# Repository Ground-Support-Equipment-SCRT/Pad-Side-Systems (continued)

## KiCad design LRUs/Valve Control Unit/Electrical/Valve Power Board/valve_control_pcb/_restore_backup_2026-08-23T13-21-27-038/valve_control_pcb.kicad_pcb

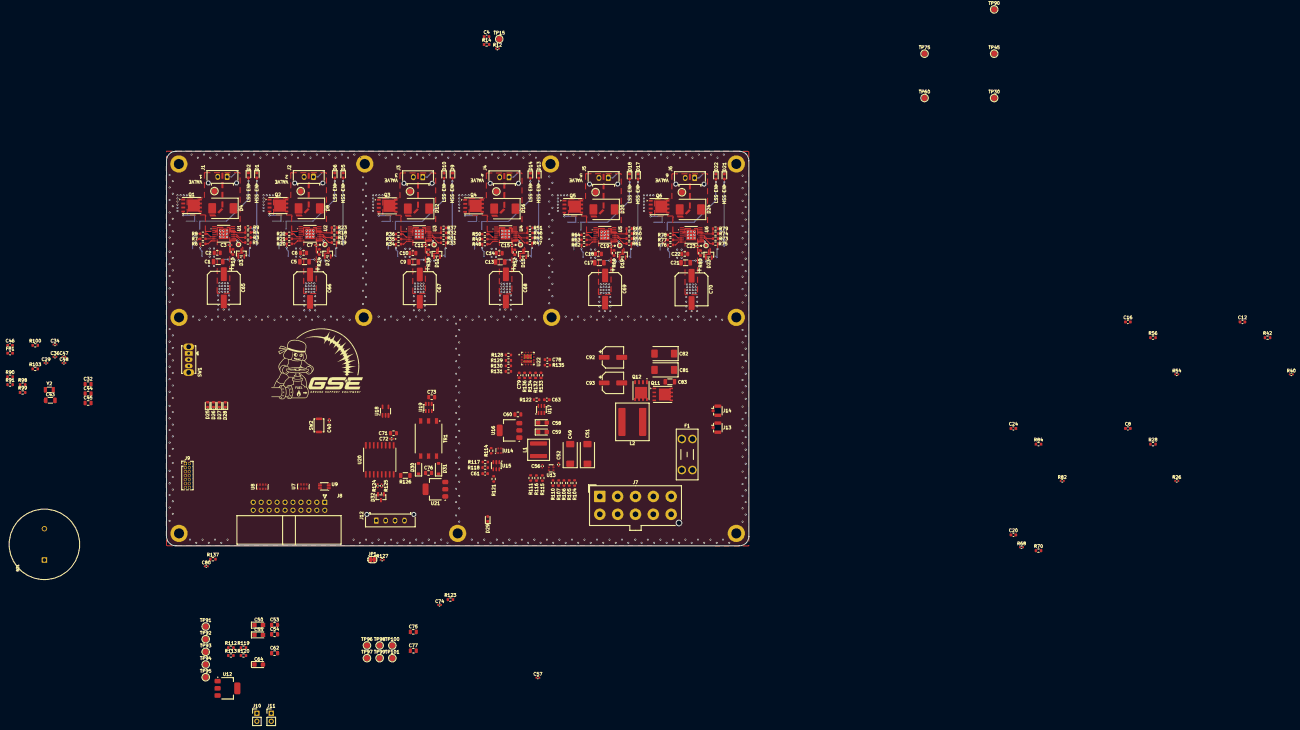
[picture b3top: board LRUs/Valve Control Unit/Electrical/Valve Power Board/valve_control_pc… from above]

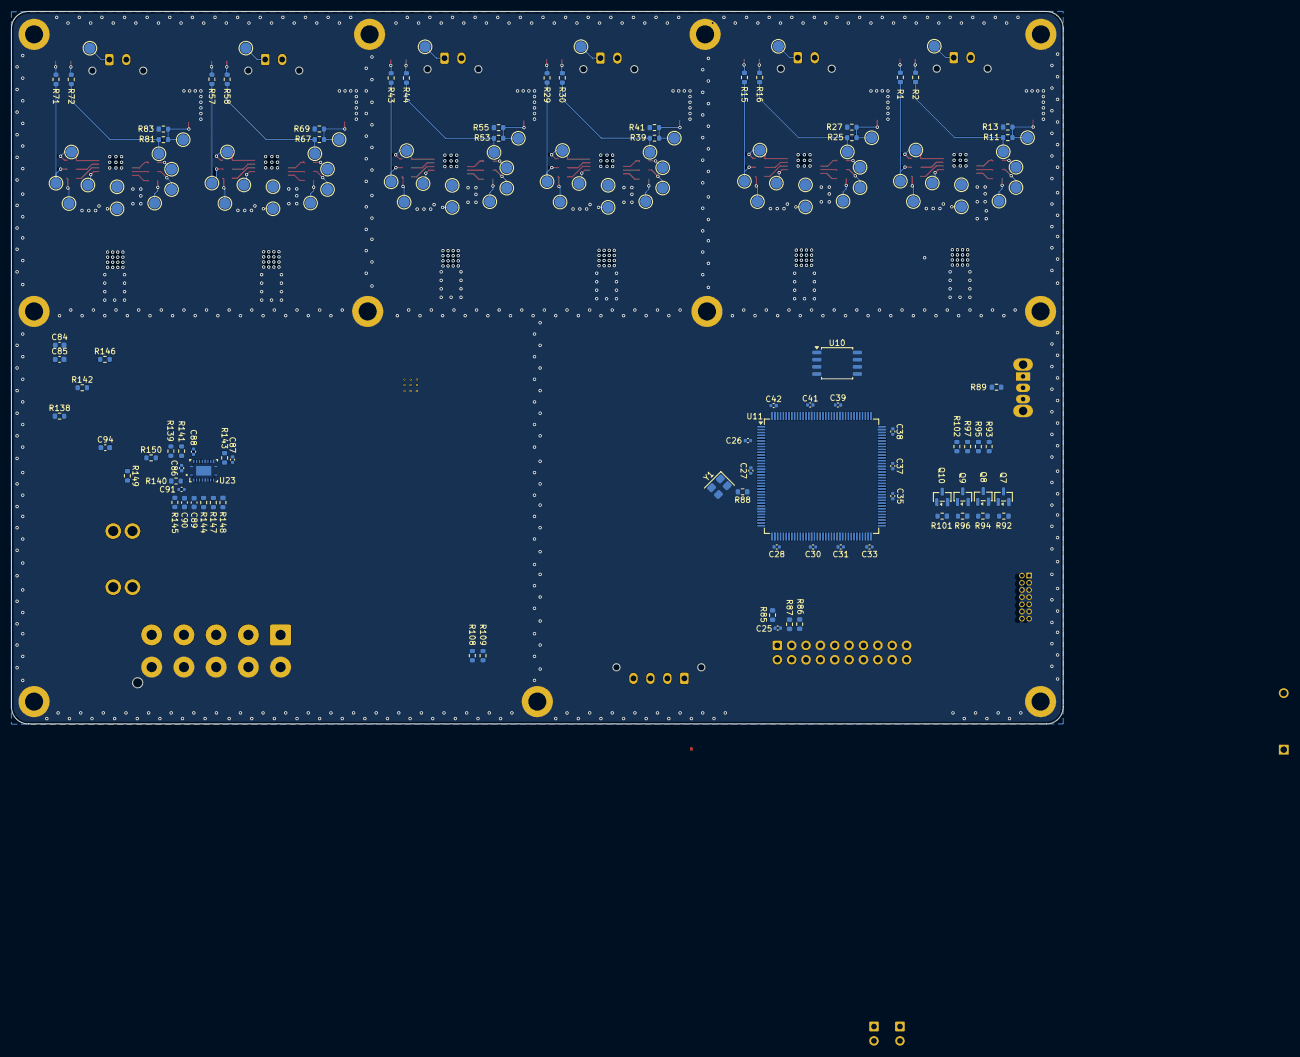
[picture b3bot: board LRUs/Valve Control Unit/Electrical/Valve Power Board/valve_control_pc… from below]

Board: 4 copper layers, 186.0 x 126.0 mm, 448 parts (154 on the bottom side), 235 nets.

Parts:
BZ1: Buzzer; MURATA_ELECTRONICS_NORTH_AMERICA_PKM22EPPH2002-B0_0
C1, C5, C9, C13, C17, C21, C43, C83: 4.7uF; C_1206_3216Metric
C2, C6, C10, C14, C18, C22: 220nF; C_0805_2012Metric
C3, C7, C11, C15, C19, C23, C26, C27, C28, C29, C30, C31, C33, C35, C37, C38, C39, C40, C41, C42, C52, C56, C57, C72, C74, C80, C86, C88: 100nF; C_0402_1005Metric
C4, C8, C12, C16, C20, C24, C46, C61, C63, C78: 10nF; C_0603_1608Metric
C25: 100pF; C_0402_1005Metric
C32, C44, C45, C53, C54, C60, C62, C71: 1uF; C_0805_2012Metric
C34, C36: 20pF; C_0402_1005Metric
C47, C48, C87, C91: 10pF; C_0402_1005Metric
C49, C51, C81, C82: 10uF; CP_EIA-7343-31_Kemet-D
C50, C55, C58, C59, C64: 10uF; CP_EIA-3216-18_Kemet-A
C65, C66, C67, C68, C69, C70: 120uF; CP_Elec_10x12.6
C73, C75, C76, C77: 10uF; C_0805_2012Metric
C79, C84: 47nF; C_0603_1608Metric
C85: 2.2uF; C_0603_1608Metric
C89, C90, C94: 330pF; C_0603_1608Metric
C92, C93: 47uF; CP_Elec_6.3x5.4
D1, D2, D5, D6, D9, D10, D13, D14, D17, D18, D21, D22, D29: RED; LED_0603_1608Metric
D3, D7, D11, D15, D19, D23: BAS21; SOT-23
D4, D8, D12, D16, D20, D24: S3M-E3/57T; D_SMC
D25, D26, D27, D28: WHITE; LED_0603_1608Metric
D30, D31: MBR0520LT; D_SOD-123
D32: SM712_SOT23; SOT-23
F1: 0297020; Fuseholder_Blade_Mini_Keystone_3568
FB1: 120R; L_0603_1608Metric
H1, H2, H3, H4, H5, H6, H7, H8, H9, H10, H11: MountingHole_Pad; MountingHole_3.2mm_M3_ISO14580_Pad
J1, J2, J3, J4, J5, J6: 0436500215; Molex_Micro-Fit_3.0_43650-0215_1x02_P3.00mm_Vertical
J7: 0768290110; Molex_Mega-Fit_76829-0110_2x05_P5.70mm_Vertical
J8: Conn_02x10_Odd_Even; IDC-Header_2x10_P2.54mm_Horizontal
J9: Conn_ST_STDC14; PinHeader_2x07_P1.27mm_Vertical
J10: Conn_01x02_Pin; PinHeader_1x02_P2.54mm_Vertical
J11: 01x02_PinHeader; PinHeader_1x02_P2.54mm_Vertical
J12: Conn_01x04; Molex_Micro-Fit_3.0_43650-0415_1x04_P3.00mm_Vertical
J13, J14: Conn_Coaxial; U.FL_Hirose_U.FL-R-SMT-1_Vertical
JP1: SolderJumper_2_Bridged; SolderJumper-2_P1.3mm_Bridged_RoundedPad1.0x1.5mm
L1: 15uH; L_Coilcraft_XAL6060-XXX
L2: 4.7uH; L_Coilcraft_XAL1010-XXX
Q1, Q2, Q3, Q4, Q5, Q6, Q11, Q12: SiR882ADP; PowerPAK_SO-8_Single
Q7, Q8, Q9, Q10: AO3400A; SOT-23
R1, R2, R10, R15, R16, R24, R29, R30, R38, R43, R44, R52, R57, R58, R66, R71, R72, R80, R86, R87, R93, R95, R97, R102: 4.7k; R_0603_1608Metric
R3, R4, R5, R6, R7, R8, R14, R17, R18, R19, R20, R21, R22, R28, R31, R32, R33, R34, R35, R36, R42, R45, R46, R47, R48, R49, R50, R56, R59, R60, R61, R62, R63, R64, R70, R73, R74, R75, R76, R77, R78, R84: 15k; R_0603_1608Metric
R9, R23, R37, R51, R65, R79, R89, R113, R121, R122, R123, R131, R135: 10k; R_0603_1608Metric
R11, R25, R39, R53, R67, R81, R90, R136, R144: 100; R_0603_1608Metric
R12, R26, R40, R54, R68, R82: 680; R_0402_1005Metric
R13, R27, R41, R55, R69, R83, R92, R94, R96, R101, R111, R114: 47k; R_0603_1608Metric
R85: 200k; R_0603_1608Metric
R88: 390; R_0603_1608Metric
R91: 1M; R_0603_1608Metric
R98, R99, R100, R103, R110, R132, R133: 0; R_0603_1608Metric
R104: 220k; R_0603_1608Metric
R105, R112, R138, R142: 20k; R_0603_1608Metric
R106, R134: 9.1k; R_0603_1608Metric
R107, R120: 51k; R_0603_1608Metric
R108, R109: 2.2k; R_0603_1608Metric
R115, R139: 68k; R_0603_1608Metric
R116: 13k; R_0603_1608Metric
R117, R119, R128: 150k; R_0603_1608Metric
R118: 100k; R_0603_1608Metric
R124, R125: 10; R_0402_1005Metric
R126: 0; R_1206_3216Metric
R127: 120; R_0402_1005Metric
R129, R146: 18k; R_0603_1608Metric
R130: 27k; R_0603_1608Metric
R137: 1k; R_0603_1608Metric
R140: 8.2k; R_0603_1608Metric
R141: 2; R_0603_1608Metric
R143: 680; R_0603_1608Metric
R145: 1.8k; R_0603_1608Metric
R147: 1.2k; R_0603_1608Metric
R148, R150: 75; R_0603_1608Metric
R149: 10; R_0603_1608Metric
SW1: SW_SPDT; SW_Slide_SPDT_Straight_CK_OS102011MS2Q
SW2: SW_Push; SW_Push_SPST_NO_Alps_SKRK
TP1, TP2, TP3, TP4, TP5, TP6, TP7, TP8, TP10, TP11, TP12, TP13, TP14, TP15, TP16, TP17, TP18, TP19, TP20, TP21, TP22, TP23, TP25, TP26, TP27, TP28, TP29, TP30, TP31, TP32, TP33, TP34, TP35, TP36, TP37, TP38, TP40, TP41, TP42, TP43, TP44, TP45, TP46, TP47, TP48, TP49, TP50, TP51, TP52, TP53, TP55, TP56, TP57, TP58, TP59, TP60, TP61, TP62, TP63, TP64, TP65, TP66, TP67, TP68, TP70, TP71, TP72, TP73, TP74, TP75, TP76, TP77, TP78, TP79, TP80, TP81, TP82, TP83, TP85, TP86, TP87, TP88, TP89, TP90, TP91, TP92, TP93, TP94, TP95, TP96, TP97, TP98, TP99, TP100, TP101: TestPoint; TestPoint_Pad_D2.0mm
TP9, TP24, TP39, TP54, TP69, TP84: TestPoint; TestPoint_Pad_D1.0mm
TR1: 750315371; Transformer_Wuerth_750315371
U1, U2, U3, U4, U5, U6: TPS27SA08CPWPR; TSSOP_CPWPR_TEX
U7, U8: TPD6E05U06RVZ; Texas_R-PUSON-N14
U9: PCA9306DC; VSSOP-8_2.3x2mm_P0.5mm
U10: W25Q128JVS; SOIC-8_5.3x5.3mm_P1.27mm
U11: STM32L496ZGTx; LQFP-144_20x20mm_P0.5mm
U12, U16: AMS1117-3.3; SOT-223-3_TabPin2
U13: TPS62933P; SOT-583-8
U14: TPS2116DRL; SOT-583-8
U15, U17: TPS22810DBV; SOT-23-6
U18: 74LVC1G17; SOT-23-5_HandSoldering
U19: SN6505BDBV; SOT-23-6
U20: ISO1450BDWR; SOIC127P1030X265-16N
U21: AMS1117-5.0; SOT-223-3_TabPin2
U22: IC_TPS259830ONRGER
U23: LM5145RGYR
Y1: 8MHz; Crystal_SMD_3225-4Pin_3.2x2.5mm
Y2: 32KHz; Crystal_SMD_3215-2Pin_3.2x1.5mm

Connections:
3V3_EXT: J8.2, U9.2 (VREF1)
+3V3: C25.1, C26.1, C27.1, C28.1, C30.1, C31.1, C33.1, C35.1, C37.1, C38.1, C39.1, C41.1, C42.1, C43.1, C44.1, FB1.1, J9.3 (VCC), R9.1, R23.1, R37.1, R51.1, R65.1, R79.1, R85.2, R86.2, R87.2, R111.1, R121.2, R135.1, SW1.3 (C), U9.7 (VREF2), U11.6 (VBAT), U11.17 (VDD), U11.39 (VDD), U11.52 (VDD), U11.62 (VDD), U11.72 (VDD), U11.84 (VDD), U11.95 (VDDIO2), U11.106 (VDDUSB), U11.108 (VDD), U11.121 (VDD), U11.131 (VDDIO2), U11.144 (VDD), U15.6 (VOUT), U18.5 (VCC)
+5V: C71.1, C72.1, C73.1, R93.2, R95.2, R97.2, R102.2, R122.2, R123.1, TR1.2, U17.6 (VOUT), U19.2 (VCC), U19.5 (EN), U20.1 (VCC1)
/Connectors/I2C_MASTER_SCL: J8.1, U7.14 (D1+), U9.3 (SCL1)
/Connectors/I2C_MASTER_SDA: J8.4, U7.13 (D1-), U9.4 (SDA1)
/Connectors/I2C_SCL: R86.1, U9.6 (SCL2)
/Connectors/I2C_SDA: R87.1, U9.5 (SDA2)
/Connectors/PIN5: J8.5, U7.12 (D2+)
/Connectors/PIN8: J8.8, U7.11 (D2-)
/Connectors/PIN9: J8.9, U7.9 (D3+)
/Connectors/PIN12: J8.12, U7.8 (D3-)
/Connectors/PIN13: J8.13, U8.14 (D1+)
/Connectors/PIN16: J8.16, U8.13 (D1-)
/Connectors/PIN17: J8.17, U8.12 (D2+)
/Connectors/PIN20: J8.20, U8.11 (D2-)
/Root/RS_485/A_RX_MAIN_N: R125.2, U20.13 (B)
/Root/RS_485/A_RX_MAIN_P: R124.2, U20.12 (A)
/Root/RS_485/RX_MAIN_N: D32.1 (A1), J12.2, JP1.1 (A), R125.1
/Root/RS_485/RX_MAIN_P: D32.2 (A2), J12.1, R124.1, R127.2
/Root/stm32_microcontroller/BOOT: R89.1, U11.138 (PH3)
/Root/stm32_microcontroller/D1: Q7.1 (G), R92.1, U11.82 (PD13)
/Root/stm32_microcontroller/D2: Q8.1 (G), R94.1, U11.81 (PD12)
/Root/stm32_microcontroller/D3: Q9.1 (G), R96.1, U11.80 (PD11)
/Root/stm32_microcontroller/D4: Q10.1 (G), R101.1, U11.79 (PD10)
/Root/stm32_microcontroller/JTDI: J9.10 (JTDI/NC), R103.1
/Root/stm32_microcontroller/JTDO: J9.8 (JTDO/SWO), R98.1
/Root/stm32_microcontroller/NRST: C40.2, J9.12 (~RST), SW2.2, U11.25 (NRST)
/Root/stm32_microcontroller/VDDA: C45.1, C46.1, FB1.2, U11.33 (VDDA)
/System Power/3V3_STATUS: R114.2, U14.8 (ST)
/System Power/5V_MAIN_PG: R111.2, TP95.1 (1_1), U13.7 (PG)
/System Power/V-3P3_LDO: C62.1, C64.1, R112.2, U14.3 (VIN1), U14.5 (MODE), U16.2 (VO)
/System Power/V-5P0_BUCK: C57.1, C58.1, C59.1, C60.1, L1.2, R108.1, R115.1, R119.2, U16.3 (VI), U17.1 (VIN)
/System Power/VEN: R106.1, R107.1, TP92.1 (1_1), U13.2 (EN)
/System Power/VFB: R115.2, R116.1, TP93.1 (1_1), U13.8 (FB)
/Valves/12V_main/SENSE_OUT: J14.1 (In), R146.2, R149.1, R150.2
/Valves/12V_main/VOUT_MAIN: C92.1, C93.1, J13.1 (In), L2.2, R128.2, R149.2, U22.1 (IN), U22.2 (IN), U22.3 (IN), U22.16 (IN), U22.25 (IN), U22.27 (EPAD), U22.28 (EPAD), U22.29 (EPAD), U22.30 (EPAD), U22.31 (EPAD), U22.32 (EPAD)
/Valves/Valve 1/12V_OUT+: D4.1 (K), J1.1, TP13.1 (1_1), U1.6 (VOUT), U1.7 (VOUT), U1.8 (VOUT), U1.9 (VOUT), U1.10 (VOUT), U1.11 (VOUT)
/Valves/Valve 1/12V_OUT-: D4.2 (A), J1.2, Q1.5 (D), TP14.1 (1_1)
/Valves/Valve 1/LFET_GATE: Q1.4 (G), R11.1, R13.1, TP11.1 (1_1)
/Valves/Valve 1/LSW_DIA_EN_PROT: R6.1, U1.16 (DIA_EN)
/Valves/Valve 1/LSW_LATCH_PROT: R5.1, U1.3 (LATCH)
/Valves/Valve 1/LSW_SEL1_PROT: R8.1, U1.14 (SEL1)
/Valves/Valve 1/LSW_SEL2_PROT: R7.1, U1.15 (SEL2)
/Valves/Valve 1/LSW_SNS_PROT: R12.2, R14.2, TP12.1 (1_1), U1.2 (SNS)
/Valves/Valve 1/VIN: C1.1, C2.1, C3.1, C5.1, C6.1, C7.1, C9.1, C10.1, C11.1, C13.1, C14.1, C15.1, C17.1, C18.1, C19.1, C21.1, C22.1, C23.1, C65.1, C66.1, C67.1, C68.1, C69.1, C70.1, TP3.1 (1_1), TP18.1 (1_1), TP33.1 (1_1), TP48.1 (1_1), TP63.1 (1_1), TP78.1 (1_1), U1.EPAD (VBB), U2.EPAD (VBB), U3.EPAD (VBB), U4.EPAD (VBB), U5.EPAD (VBB), U6.EPAD (VBB), U22.17 (OUT), U22.18 (OUT), U22.19 (OUT), U22.20 (OUT), U22.21 (OUT), U22.22 (OUT), U22.23 (OUT), U22.24 (OUT)
/Valves/Valve 1/~LSW_ST_PROT: R4.1, R9.2, U1.5 (~ST)
/Valves/Valve 2/12V_OUT+: D8.1 (K), J2.1, TP28.1 (1_1), U2.6 (VOUT), U2.7 (VOUT), U2.8 (VOUT), U2.9 (VOUT), U2.10 (VOUT), U2.11 (VOUT)
/Valves/Valve 2/12V_OUT-: D8.2 (A), J2.2, Q2.5 (D), TP29.1 (1_1)
/Valves/Valve 2/LFET_GATE: Q2.4 (G), R25.1, R27.1, TP26.1 (1_1)
/Valves/Valve 2/LSW_DIA_EN_PROT: R20.1, U2.16 (DIA_EN)
/Valves/Valve 2/LSW_LATCH_PROT: R19.1, U2.3 (LATCH)
/Valves/Valve 2/LSW_SEL1_PROT: R22.1, U2.14 (SEL1)
/Valves/Valve 2/LSW_SEL2_PROT: R21.1, U2.15 (SEL2)
/Valves/Valve 2/LSW_SNS_PROT: R26.2, R28.2, TP27.1 (1_1), U2.2 (SNS)
/Valves/Valve 2/~LSW_ST_PROT: R18.1, R23.2, U2.5 (~ST)
/Valves/Valve 3/12V_OUT+: D12.1 (K), J3.1, TP43.1 (1_1), U3.6 (VOUT), U3.7 (VOUT), U3.8 (VOUT), U3.9 (VOUT), U3.10 (VOUT), U3.11 (VOUT)
/Valves/Valve 3/12V_OUT-: D12.2 (A), J3.2, Q3.5 (D), TP44.1 (1_1)
/Valves/Valve 3/LFET_GATE: Q3.4 (G), R39.1, R41.1, TP41.1 (1_1)
/Valves/Valve 3/LSW_DIA_EN_PROT: R34.1, U3.16 (DIA_EN)
/Valves/Valve 3/LSW_LATCH_PROT: R33.1, U3.3 (LATCH)
/Valves/Valve 3/LSW_SEL1_PROT: R36.1, U3.14 (SEL1)
/Valves/Valve 3/LSW_SEL2_PROT: R35.1, U3.15 (SEL2)
/Valves/Valve 3/LSW_SNS_PROT: R40.2, R42.2, TP42.1 (1_1), U3.2 (SNS)
/Valves/Valve 3/~LSW_ST_PROT: R32.1, R37.2, U3.5 (~ST)
/Valves/Valve 4/12V_OUT+: D16.1 (K), J4.1, TP58.1 (1_1), U4.6 (VOUT), U4.7 (VOUT), U4.8 (VOUT), U4.9 (VOUT), U4.10 (VOUT), U4.11 (VOUT)
/Valves/Valve 4/12V_OUT-: D16.2 (A), J4.2, Q4.5 (D), TP59.1 (1_1)
/Valves/Valve 4/LFET_GATE: Q4.4 (G), R53.1, R55.1, TP56.1 (1_1)
/Valves/Valve 4/LSW_DIA_EN_PROT: R48.1, U4.16 (DIA_EN)
/Valves/Valve 4/LSW_LATCH_PROT: R47.1, U4.3 (LATCH)
/Valves/Valve 4/LSW_SEL1_PROT: R50.1, U4.14 (SEL1)
/Valves/Valve 4/LSW_SEL2_PROT: R49.1, U4.15 (SEL2)
/Valves/Valve 4/LSW_SNS_PROT: R54.2, R56.2, TP57.1 (1_1), U4.2 (SNS)
/Valves/Valve 4/~LSW_ST_PROT: R46.1, R51.2, U4.5 (~ST)
/Valves/Valve 5/12V_OUT+: D20.1 (K), J5.1, TP73.1 (1_1), U5.6 (VOUT), U5.7 (VOUT), U5.8 (VOUT), U5.9 (VOUT), U5.10 (VOUT), U5.11 (VOUT)
/Valves/Valve 5/12V_OUT-: D20.2 (A), J5.2, Q5.5 (D), TP74.1 (1_1)
/Valves/Valve 5/LFET_GATE: Q5.4 (G), R67.1, R69.1, TP71.1 (1_1)
/Valves/Valve 5/LSW_DIA_EN_PROT: R62.1, U5.16 (DIA_EN)
/Valves/Valve 5/LSW_LATCH_PROT: R61.1, U5.3 (LATCH)
/Valves/Valve 5/LSW_SEL1_PROT: R64.1, U5.14 (SEL1)
/Valves/Valve 5/LSW_SEL2_PROT: R63.1, U5.15 (SEL2)
/Valves/Valve 5/LSW_SNS_PROT: R68.2, R70.2, TP72.1 (1_1), U5.2 (SNS)
/Valves/Valve 5/~LSW_ST_PROT: R60.1, R65.2, U5.5 (~ST)
/Valves/Valve 6/12V_OUT+: D24.1 (K), J6.1, TP88.1 (1_1), U6.6 (VOUT), U6.7 (VOUT), U6.8 (VOUT), U6.9 (VOUT), U6.10 (VOUT), U6.11 (VOUT)
/Valves/Valve 6/12V_OUT-: D24.2 (A), J6.2, Q6.5 (D), TP89.1 (1_1)
/Valves/Valve 6/LFET_GATE: Q6.4 (G), R81.1, R83.1, TP86.1 (1_1)
/Valves/Valve 6/LSW_DIA_EN_PROT: R76.1, U6.16 (DIA_EN)
/Valves/Valve 6/LSW_LATCH_PROT: R75.1, U6.3 (LATCH)
/Valves/Valve 6/LSW_SEL1_PROT: R78.1, U6.14 (SEL1)
/Valves/Valve 6/LSW_SEL2_PROT: R77.1, U6.15 (SEL2)
/Valves/Valve 6/LSW_SNS_PROT: R82.2, R84.2, TP87.1 (1_1), U6.2 (SNS)
/Valves/Valve 6/~LSW_ST_PROT: R74.1, R79.2, U6.5 (~ST)
/Valves/master_efuse/DVDT: C78.1, U22.15 (DVDT/BGATE)
/Valves/master_efuse/ILIM: R136.2, U22.8 (ILIM)
/Valves/master_efuse/IMON_IC: R134.2, R137.2, U22.9 (IMON)
/Valves/master_efuse/ITIM: C79.1, U22.7 (ITIMER)
EFUSE_IMON: C80.1, R137.1
EFUSE_PG: R135.2, U22.13 (PG)
GND: BZ1.2 (-), C1.2, C2.2, C4.2, C5.2, C6.2, C8.2, C9.2, C10.2, C12.2, C13.2, C14.2, C16.2, C17.2, C18.2, C20.2, C21.2, C22.2, C24.2, C25.2, C26.2, C27.2, C28.2, C29.2, C30.2, C31.2, C32.2, C33.2, C34.2, C35.2, C36.2, C37.2, C38.2, C39.2, C40.1, C41.2, C42.2, C43.2, C44.2, C45.2, C46.2, C47.2, C48.2, C49.2, C50.2, C51.2, C52.2, C53.2, C54.2, C55.2, C57.2, C58.2, C59.2, C60.2, C61.2, C62.2, C63.2, C64.2, C65.2, C66.2, C67.2, C68.2, C69.2, C70.2, C71.2, C72.2, C73.2, C78.2, C79.2, C80.2, C81.2, C82.2, C83.2, C84.2, C85.2, C86.2, C87.2, C92.2, C93.2, D1.1 (K), D2.1 (K), D3.1 (A), D5.1 (K), D6.1 (K), D7.1 (A), D9.1 (K), D10.1 (K), D11.1 (A), D13.1 (K), D14.1 (K), D15.1 (A), D17.1 (K), D18.1 (K), D19.1 (A), D21.1 (K), D22.1 (K), D23.1 (A), D29.1 (K), H1.1 (1_1), H2.1 (1_1), H3.1 (1_1), H4.1 (1_1), H5.1 (1_1), H6.1 (1_1), H7.1 (1_1), H8.1 (1_1), H9.1 (1_1), H10.1 (1_1), H11.1 (1_1), J7.6, J7.7, J7.8, J7.9, J7.10, J8.3, J8.6, J8.7, J8.10, J8.11, J8.14, J8.15, J8.18, J8.19, J9.5 (GND), J9.7 (GND), J9.11 (GNDDetect), J10.2, J11.2, J13.2 (Ext), J14.2 (Ext), Q1.1 (S), Q1.2 (S), Q1.3 (S), Q2.1 (S), Q2.2 (S), Q2.3 (S), Q3.1 (S), Q3.2 (S), Q3.3 (S), Q4.1 (S), Q4.2 (S), Q4.3 (S), Q5.1 (S), Q5.2 (S), Q5.3 (S), Q6.1 (S), Q6.2 (S), Q6.3 (S), Q7.2 (S), Q8.2 (S), Q9.2 (S), Q10.2 (S), Q12.1 (S), Q12.2 (S), Q12.3 (S), R10.1, R12.1, R13.2, R24.1, R26.1, R27.2, R38.1, R40.1, R41.2, R52.1, R54.1, R55.2, R66.1, R68.1, R69.2, R80.1, R82.1, R83.2, R91.1, R92.2, R94.2, R96.2, R101.2, R107.2, R110.1, R113.2, R116.2, R118.1, R120.2, R131.1, R132.1, R133.1, R134.1, R136.1, R138.1, R140.1, R148.1, SW1.1 (A), SW2.1, TP10.1 (1_1), TP25.1 (1_1), TP40.1 (1_1), TP55.1 (1_1), TP70.1 (1_1), TP85.1 (1_1), U7.5 (GND), U7.10 (GND), U8.5 (GND), U8.10 (GND), U9.1 (GND), U11.16 (VSS), U11.30 (VSSA), U11.31 (VREF-), U11.38 (VSS), U11.51 (VSS), U11.61 (VSS), U11.71 (VSS), U11.83 (VSS), U11.94 (VSS), U11.107 (VSS), U11.120 (VSS), U11.130 (VSS), U11.143 (VSS), U12.1 (GND), U13.4 (GND), U14.1 (GND), U15.2 (GND), U16.1 (GND), U17.2 (GND), U18.3 (GND), U19.4 (GND), U19.6 (CLK), U20.2 (GND1), U20.8 (GND1__1), U22.4 (GND), U22.5 (GND), U22.14 (GND), U22.26 (GND), U22.33 (EPAD), U22.34 (EPAD), U22.35 (EPAD), U23.6 (AGND), U23.12 (PGND), U23.15 (EP), U23.21 (EP), Y1.2, Y1.4
ISOGND: C74.2, C75.2, C76.2, C77.2, D32.3 (common), J12.3, TR1.5, U20.9 (GND2), U20.15 (GND2__1), U21.1 (GND)
MODGND: C3.2, C7.2, C11.2, C15.2, C19.2, C23.2, D3.3 (K), D7.3 (K), D11.3 (K), D15.3 (K), D19.3 (K), D23.3 (K), R10.2, R24.2, R38.2, R52.2, R66.2, R80.2, TP9.1 (1_1), TP24.1 (1_1), TP39.1 (1_1), TP54.1 (1_1), TP69.1 (1_1), TP84.1 (1_1), U1.1 (GND), U2.1 (GND), U3.1 (GND), U4.1 (GND), U5.1 (GND), U6.1 (GND)
unnamed: BZ1.1 (+), R90.2
unnamed: C36.1, R88.2, Y1.3
unnamed: C89.2, C90.1
unnamed: C91.2, R145.2
unnamed: C94.1, R150.1
unnamed: D1.2 (A), R1.1
unnamed: D2.2 (A), R2.1
unnamed: D5.2 (A), R15.1
unnamed: D6.2 (A), R16.1
unnamed: D9.2 (A), R29.1
unnamed: D10.2 (A), R30.1
unnamed: D13.2 (A), R43.1
unnamed: D14.2 (A), R44.1
unnamed: D17.2 (A), R57.1
unnamed: D18.2 (A), R58.1
unnamed: D21.2 (A), R71.1
unnamed: D22.2 (A), R72.1
unnamed: D25.2 (A), R93.1
unnamed: D25.1 (K), Q7.3 (D)
unnamed: D26.2 (A), R95.1
unnamed: D26.1 (K), Q8.3 (D)
unnamed: D27.2 (A), R97.1
unnamed: D27.1 (K), Q9.3 (D)
unnamed: D28.2 (A), R102.1
unnamed: D28.1 (K), Q10.3 (D)
unnamed: D29.2 (A), R109.2
unnamed: D30.2 (A), TP98.1 (1_1), TR1.4
unnamed: C76.1, D30.1 (K), D31.1 (K), R126.2, TP100.1 (1_1), U21.3 (VI)
unnamed: D31.2 (A), TP99.1 (1_1), TR1.6
unnamed: F1.1, J7.1, J7.2, J7.3, J7.4, J7.5
unnamed: J9.13 (VCP_RX), R99.2
unnamed: J9.14 (VCP_TX), R100.2
unnamed: J10.1, R117.1, R118.2, U15.3 (EN/UVLO)
unnamed: J11.1, R119.1, R120.1, U17.3 (EN/UVLO)
unnamed: JP1.2 (B), R127.1
unnamed: Q11.4 (G), U23.18 (HO)
unnamed: C88.2, L2.1, Q11.1 (S), Q11.2 (S), Q11.3 (S), Q12.5 (D), R143.1, U23.19 (SW)
unnamed: Q12.4 (G), U23.13 (LO)
unnamed: R104.1, R105.2
unnamed: R105.1, R106.2
unnamed: R108.2, R109.1
unnamed: R128.1, R129.2
unnamed: R144.2, R145.1
unnamed: R147.1, R148.2
unnamed: R89.2, SW1.2 (B)
unnamed: R3.1, U1.4 (EN)
unnamed: R17.1, U2.4 (EN)
unnamed: R31.1, U3.4 (EN)
unnamed: R45.1, U4.4 (EN)
unnamed: R59.1, U5.4 (EN)
unnamed: R73.1, U6.4 (EN)
unnamed: R85.1, U9.8 (EN)
unnamed: C48.1, U11.8 (RCC_OSC32_IN), Y2.1
unnamed: C47.1, U11.9 (RCC_OSC32_OUT), Y2.2
unnamed: R90.1, R91.2, U11.68 (PE15)
unnamed: C34.1, U11.23 (RCC_OSC_IN), Y1.1
unnamed: R88.1, U11.24 (RCC_OSC_OUT)
unnamed: C29.1, C32.1, U11.32 (VREF+)
unnamed: C54.1, C55.1, U12.2 (VO), U14.6 (VIN2)
unnamed: C56.1, U13.6 (BST)
unnamed: R110.2, U13.1 (RT)
unnamed: C56.2, L1.1, U13.5 (SW)
unnamed: R112.1, R113.1, U14.4 (PR1)
unnamed: C61.1, U15.4 (CT)
unnamed: R121.1, U15.5 (QOD)
unnamed: R114.1, R117.2, U14.2 (VOUT), U14.7 (VOUT), U15.1 (VIN)
unnamed: C63.1, U17.4 (CT)
unnamed: R122.1, U17.5 (QOD)
unnamed: TP96.1 (1_1), TR1.3, U19.1 (D1)
unnamed: TP97.1 (1_1), TR1.1, U19.3 (D2)
unnamed: R123.2, U18.2, U20.3 (R)
unnamed: C74.1, C75.1, C77.1, R126.1, TP101.1 (1_1), U20.16 (VCC2), U21.2 (VO)
unnamed: R129.1, R130.2, U22.6 (EN/UVLO)
unnamed: R133.2, U22.11 (NRETRY)
unnamed: R130.1, R131.2, U22.12 (OVLO)
unnamed: R132.2, U22.10 (RETRY_DLY)
unnamed: C88.1, U23.17 (BST)
unnamed: C90.2, C91.1, U23.4 (COMP)
unnamed: R139.1, R140.2, U23.1 (EN_UVLO)
unnamed: C89.1, C94.2, R144.1, R146.1, R147.2, U23.5 (FB)
unnamed: C87.1, R143.2, U23.11 (ILIM)
unnamed: R138.2, U23.2 (RT)
unnamed: C84.1, U23.3 (SS_TRK)
unnamed: R142.2, U23.8 (SYNCIN)
unnamed: C85.1, R142.1, U23.14 (VCC)
unnamed: C86.1, R141.1, U23.20 (VIN)
VALVE1.LSW_DIA_EN: R6.2, TP6.1 (1_1)
VALVE1.LSW_LATCH: R5.2, TP5.1 (1_1)
VALVE1.LSW_SEL1: R8.2, TP8.1 (1_1)
VALVE1.LSW_SEL2: R7.2, TP7.1 (1_1)
VALVE1.~LSW_ST: R4.2, TP4.1 (1_1)
VALVE1_HSS_EN: R1.2, R3.2, TP1.1 (1_1)
VALVE1_LSS_EN: R2.2, R11.2, TP2.1 (1_1)
VALVE1_LSW_SNS: C4.1, R14.1, TP15.1 (1_1)
VALVE2.LSW_DIA_EN: R20.2, TP21.1 (1_1)
VALVE2.LSW_LATCH: R19.2, TP20.1 (1_1)
VALVE2.LSW_SEL1: R22.2, TP23.1 (1_1)
VALVE2.LSW_SEL2: R21.2, TP22.1 (1_1)
VALVE2.~LSW_ST: R18.2, TP19.1 (1_1)
VALVE2_HSS_EN: R15.2, R17.2, TP16.1 (1_1)
VALVE2_LSS_EN: R16.2, R25.2, TP17.1 (1_1)
VALVE2_LSW_SNS: C8.1, R28.1, TP30.1 (1_1)
VALVE3.LSW_DIA_EN: R34.2, TP36.1 (1_1)
VALVE3.LSW_LATCH: R33.2, TP35.1 (1_1)
VALVE3.LSW_SEL1: R36.2, TP38.1 (1_1)
VALVE3.LSW_SEL2: R35.2, TP37.1 (1_1)
VALVE3.~LSW_ST: R32.2, TP34.1 (1_1)
VALVE3_HSS_EN: R29.2, R31.2, TP31.1 (1_1)
VALVE3_LSS_EN: R30.2, R39.2, TP32.1 (1_1)
VALVE3_LSW_SNS: C12.1, R42.1, TP45.1 (1_1)
VALVE4.LSW_DIA_EN: R48.2, TP51.1 (1_1)
VALVE4.LSW_LATCH: R47.2, TP50.1 (1_1)
VALVE4.LSW_SEL1: R50.2, TP53.1 (1_1)
VALVE4.LSW_SEL2: R49.2, TP52.1 (1_1)
VALVE4.~LSW_ST: R46.2, TP49.1 (1_1)
VALVE4_HSS_EN: R43.2, R45.2, TP46.1 (1_1)
VALVE4_LSS_EN: R44.2, R53.2, TP47.1 (1_1)
VALVE4_LSW_SNS: C16.1, R56.1, TP60.1 (1_1)
VALVE5.LSW_DIA_EN: R62.2, TP66.1 (1_1)
VALVE5.LSW_LATCH: R61.2, TP65.1 (1_1)
VALVE5.LSW_SEL1: R64.2, TP68.1 (1_1)
VALVE5.LSW_SEL2: R63.2, TP67.1 (1_1)
VALVE5.~LSW_ST: R60.2, TP64.1 (1_1)
VALVE5_HSS_EN: R57.2, R59.2, TP61.1 (1_1)
VALVE5_LSS_EN: R58.2, R67.2, TP62.1 (1_1)
VALVE5_LSW_SNS: C20.1, R70.1, TP75.1 (1_1)
VALVE6.LSW_DIA_EN: R76.2, TP81.1 (1_1)
VALVE6.LSW_LATCH: R75.2, TP80.1 (1_1)
VALVE6.LSW_SEL1: R78.2, TP83.1 (1_1)
VALVE6.LSW_SEL2: R77.2, TP82.1 (1_1)
VALVE6.~LSW_ST: R74.2, TP79.1 (1_1)
VALVE6_HSS_EN: R71.2, R73.2, TP76.1 (1_1)
VALVE6_LSS_EN: R72.2, R81.2, TP77.1 (1_1)
VALVE6_LSW_SNS: C24.1, R84.1, TP90.1 (1_1)
VBUS: C49.1, C50.1, C51.1, C52.1, C53.1, C81.1, C82.1, C83.1, F1.2, Q11.5 (D), R104.2, R139.2, R141.2, TP91.1 (1_1), U12.3 (VI), U13.3 (VIN)

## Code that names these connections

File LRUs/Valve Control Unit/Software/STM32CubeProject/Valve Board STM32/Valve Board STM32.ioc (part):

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Mcu.Name=STM32L496Z(E-G)Tx
Mcu.Package=LQFP144
Mcu.UserName=STM32L496ZGTx
PA0.Signal=ADCx_IN5
PA1.Signal=ADCx_IN6
PA11.Mode=Device_Only
PA11.Signal=USB_OTG_FS_DM
PA12.Mode=Device_Only
PA12.Signal=USB_OTG_FS_DP
PA13\ (JTMS/SWDIO).Mode=Serial_Wire
PA13\ (JTMS/SWDIO).Signal=SYS_JTMS-SWDIO
PA14\ (JTCK/SWCLK).Mode=Serial_Wire
PA14\ (JTCK/SWCLK).Signal=SYS_JTCK-SWCLK
PA2.Mode=Single Bank 1
PA2.Signal=QUADSPI_BK1_NCS
PA3.Signal=ADCx_IN8
PA4.Mode=NSS_Signal_Hard_Output
PA4.Signal=SPI1_NSS
PA5.Mode=Full_Duplex_Master
PA5.Signal=SPI1_SCK
PA6.Mode=Full_Duplex_Master
PA6.Signal=SPI1_MISO
PA7.Mode=Full_Duplex_Master
PA7.Signal=SPI1_MOSI
PA9.Mode=Activate_VBUS
PA9.Signal=USB_OTG_FS_VBUS
PB1.Mode=Hardware Flow Control (RS485)
PB1.Signal=USART3_DE
PB10.Signal=GPIO_Output
PB3\ (JTDO/TRACESWO).Signal=GPIO_Output
PB4\ (NJTRST).Signal=GPIO_Input
PB5.Signal=GPIO_Output
PB6.Signal=GPIO_Output
PB7.Signal=GPIO_Output
PB8.Signal=GPIO_Output
PB9.Signal=GPIO_Output
PC0.Signal=ADCx_IN1
PC1.Signal=ADCx_IN2
PC10.Mode=SD_4_bits_Wide_bus
PC10.Signal=SDMMC1_D2
PC11.Mode=SD_4_bits_Wide_bus
PC11.Signal=SDMMC1_D3
PC12.Mode=SD_4_bits_Wide_bus
PC12.Signal=SDMMC1_CK
PC13.Mode=SYS_WakeUp1
PC13.Signal=SYS_WKUP2
PC14-OSC32_IN\ (PC14).Mode=LSE-External-Oscillator
PC14-OSC32_IN\ (PC14).Signal=RCC_OSC32_IN
PC15-OSC32_OUT\ (PC15).Mode=LSE-External-Oscillator
PC15-OSC32_OUT\ (PC15).Signal=RCC_OSC32_OUT
PC2.Signal=ADCx_IN3
PC3.Signal=ADCx_IN4
PC4.Mode=Asynchronous
PC4.Signal=USART3_TX
PC5.Mode=Asynchronous
PC5.Signal=USART3_RX
PC8.Mode=SD_4_bits_Wide_bus
PC8.Signal=SDMMC1_D0
PC9.Mode=SD_4_bits_Wide_bus
PC9.Signal=SDMMC1_D1
PD0.GPIOParameters=GPIO_Label
PD0.GPIO_Label=VALVE1_LSS_EN
PD0.Signal=GPIO_Output
PD1.GPIOParameters=GPIO_Label
PD1.GPIO_Label=VALVE1_HSS_EN
PD1.Signal=GPIO_Output
PD2.Mode=SD_4_bits_Wide_bus
PD2.Signal=SDMMC1_CMD
PD3.GPIOParameters=GPIO_Label
PD3.GPIO_Label=VALVE1_LSW_SEL1
PD3.Signal=GPIO_Input
PD4.GPIOParameters=GPIO_Label
PD4.GPIO_Label=VALVE1_LSW_SEL2
PD4.Signal=GPIO_Input
PD5.GPIOParameters=GPIO_Label
PD5.GPIO_Label=VALVE1_LSW_DIA_EN
PD5.Signal=GPIO_Input
PD6.GPIOParameters=GPIO_Label
PD6.GPIO_Label=VALVE1_LSW_LATCH
PD6.Signal=GPIO_Input
PD7.GPIOParameters=GPIO_Label
PD7.GPIO_Label=VALVE1_LSW_STn
PD7.Signal=GPIO_Output
PE0.Signal=GPIO_Output
PE1.Signal=GPIO_Input
PE10.Signal=GPIO_Output
PE11.Signal=GPIO_Output
PE12.Signal=GPIO_Output
PE13.Signal=GPIO_Output
PE14.Signal=GPIO_Output
PE15.Signal=GPIO_Output
PE2.Signal=GPIO_Output
PE3.Signal=GPIO_Output
PE4.Signal=GPIO_Output
PE5.Signal=GPIO_Output
PE6.Signal=GPIO_Output
PE7.Signal=GPIO_Output
PE8.Signal=GPIO_Output
PE9.Signal=GPIO_Input
PF0.Signal=GPIO_Output
PF1.Signal=GPIO_Input
PF10.Mode=Single Bank 1
PF10.Signal=QUADSPI_CLK
PF13.Signal=GPIO_Input
PF14.Signal=GPIO_Output
PF15.Signal=GPIO_Output
PF6.Mode=Single Bank 1
PF6.Signal=QUADSPI_BK1_IO3
PF7.Mode=Single Bank 1
PF7.Signal=QUADSPI_BK1_IO2
PF8.Mode=Single Bank 1
PF8.Signal=QUADSPI_BK1_IO0
PF9.Mode=Single Bank 1
PF9.Signal=QUADSPI_BK1_IO1
PG0.Signal=GPIO_Output
PG1.Signal=GPIO_Output
PG10.Signal=GPIO_Output
PG11.Signal=GPIO_Output
PG12.Signal=GPIO_Output
PG13.Mode=I2C
PG13.Signal=I2C1_SDA
PG14.Mode=I2C
PG14.Signal=I2C1_SCL
PG15.Signal=GPIO_Output
PG7.Mode=I2C
PG7.Signal=I2C3_SCL
PG8.Mode=I2C
PG8.Signal=I2C3_SDA
PG9.Signal=GPIO_Output
PH0-OSC_IN\ (PH0).Mode=HSE-External-Oscillator
PH0-OSC_IN\ (PH0).Signal=RCC_OSC_IN
PH1-OSC_OUT\ (PH1).Mode=HSE-External-Oscillator
PH1-OSC_OUT\ (PH1).Signal=RCC_OSC_OUT
RCC.HSE_VALUE=8000000
board=custom
